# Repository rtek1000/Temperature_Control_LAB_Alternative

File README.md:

# Temperature_Control_LAB_Alternative
Alternative version of the Arduino "Temperature Control LAB" shield for code testing
- Transistor BC338
- Heater element: 27R 5W resistor
- Temperature sensor LM35

--------

## Licence:

Note: This library is free software; you can redistribute it and/or modify it under the terms of the GNU Lesser General Public License as published by the Free Software Foundation; either version 2.1 of the License, or (at your option) any later version.

This library is distributed in the hope that it will be useful, but WITHOUT ANY WARRANTY; without even the implied warranty of MERCHANTABILITY or FITNESS FOR A PARTICULAR PURPOSE.

#### Hardware:
Released under CERN OHL 1.2: https://ohwr.org/cernohl

------

Test codes:
[sTune](https://github.com/Dlloydev/sTune) (MIT license)

- This is an open loop PID autotuner using a novel s-curve inflection point test method. Tuning parameters are typically determined in about ½Tau on a first-order system with time delay. Full 5Tau testing and multiple serial output options are provided.

    - Compatible with [PID_v1](https://github.com/br3ttb/Arduino-PID-Library), [QuickPID](https://github.com/Dlloydev/QuickPID) and others
    - Serial output option for [PID Tuner](https://pidtuner.com/#/)
    - Tested using [Temperature Control Lab](http://apmonitor.com/pdc/index.php/Main/ArduinoTemperatureControl)

Source: https://forum.arduino.cc/t/stune-pid-autotune-library/941939

------

Temperature Control Lab - Original board:
- Transistor TIP31
- Heatsink
- Temperature sensor TMP36

Source: https://scholarsarchive.byu.edu/cgi/viewcontent.cgi?params=/context/facpub/article/4888/&path_info=2020_park_tclab.pdf

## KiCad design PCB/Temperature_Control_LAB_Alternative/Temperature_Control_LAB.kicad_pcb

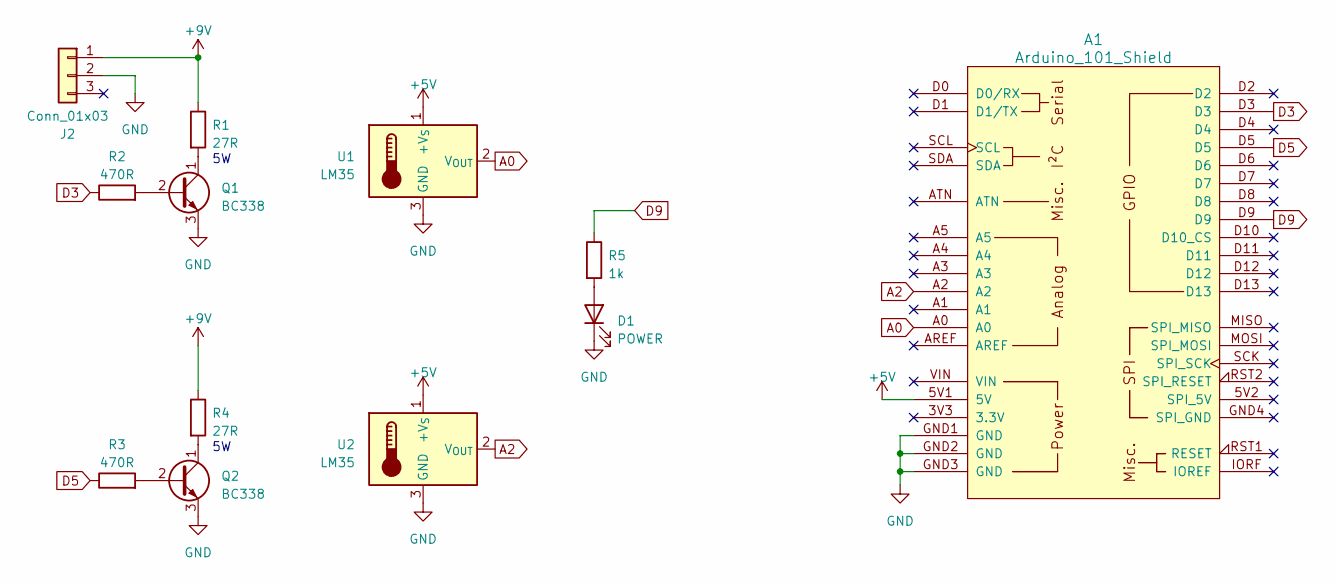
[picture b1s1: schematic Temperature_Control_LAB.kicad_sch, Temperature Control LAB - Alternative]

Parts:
A1: Arduino_101_Shield; Arduino_101_Shield_Clean
D1: POWER; LED_D3.0mm
J2: Conn_01x03; BarrelJack_Kycon_KLDX-0202-xC_Horizontal
Q1, Q2: BC338; TO-92_Inline
R1, R4: 27R; R_Axial_DIN0516_L15.5mm_D5.0mm_P20.32mm_Horizontal
R2, R3: 470R; R_Axial_DIN0204_L3.6mm_D1.6mm_P7.62mm_Horizontal
R5: 1k; R_Axial_DIN0204_L3.6mm_D1.6mm_P7.62mm_Horizontal
U1, U2: LM35; TO-92_Inline

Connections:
+5V: A1.5V1 (5V), U1.1 (+V_{S}), U2.1 (+V_{S})
+9V: J2.1, R1.1, R4.1
A0: A1.A0, U1.2 (V_{OUT})
A2: A1.A2, U2.2 (V_{OUT})
D3: A1.D3, R2.1
D5: A1.D5, R3.1
D9: A1.D9, R5.1
GND: A1.GND1 (GND), A1.GND2 (GND), A1.GND3 (GND), D1.1 (K), J2.2, Q1.3 (E), Q2.3 (E), U1.3 (GND), U2.3 (GND)
unnamed: D1.2 (A), R5.2
unnamed: Q1.2 (B), R2.2
unnamed: Q1.1 (C), R1.2
unnamed: Q2.2 (B), R3.2
unnamed: Q2.1 (C), R4.2

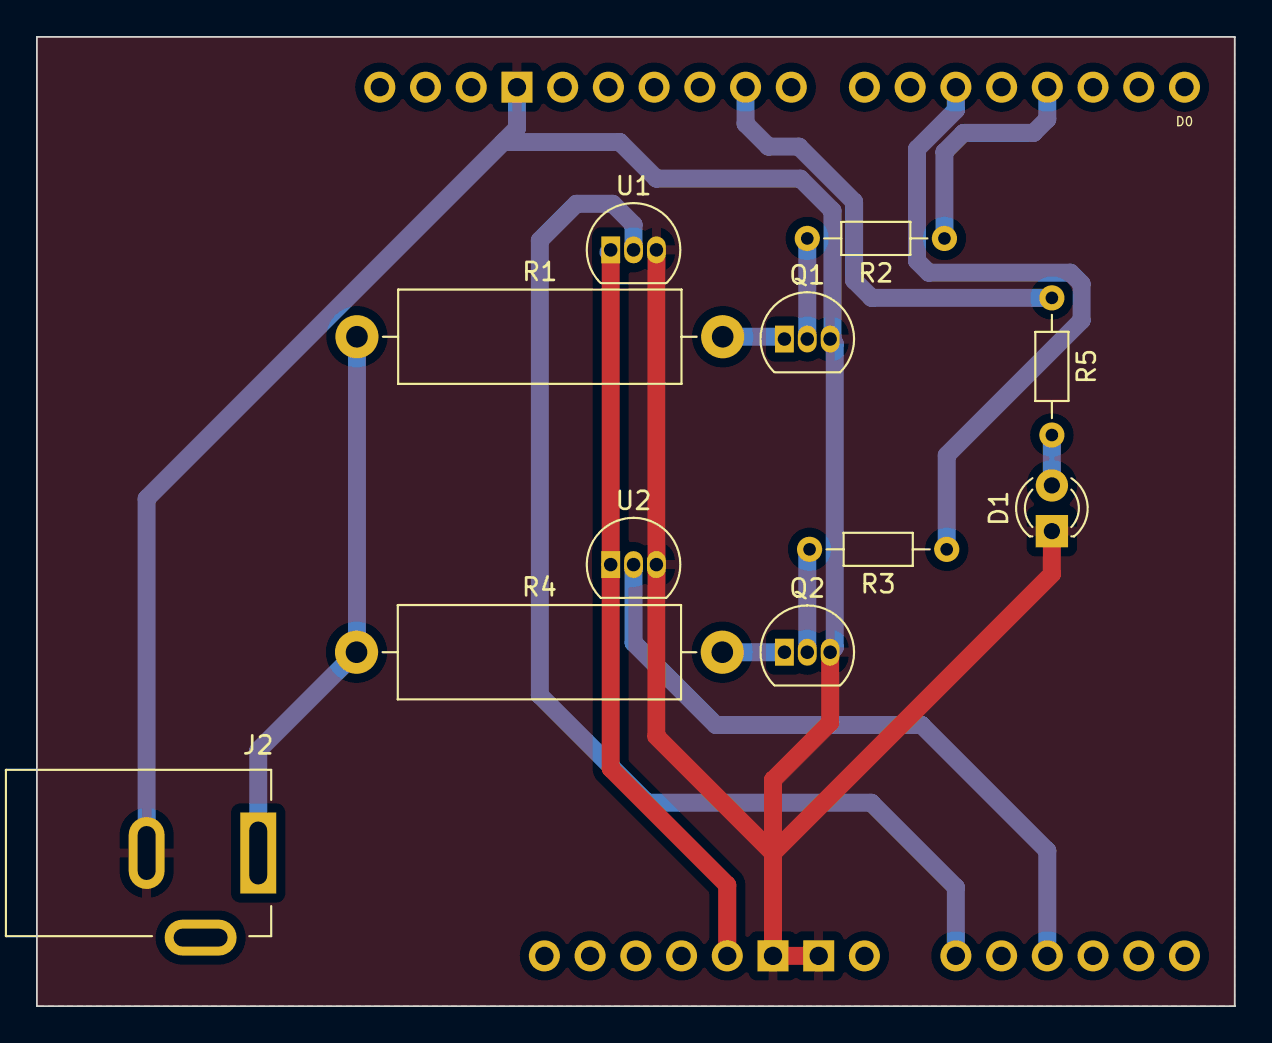
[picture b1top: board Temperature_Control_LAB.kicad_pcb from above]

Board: 2 copper layers, 66.5 x 53.8 mm, 12 parts (0 on the bottom side), 13 nets.
